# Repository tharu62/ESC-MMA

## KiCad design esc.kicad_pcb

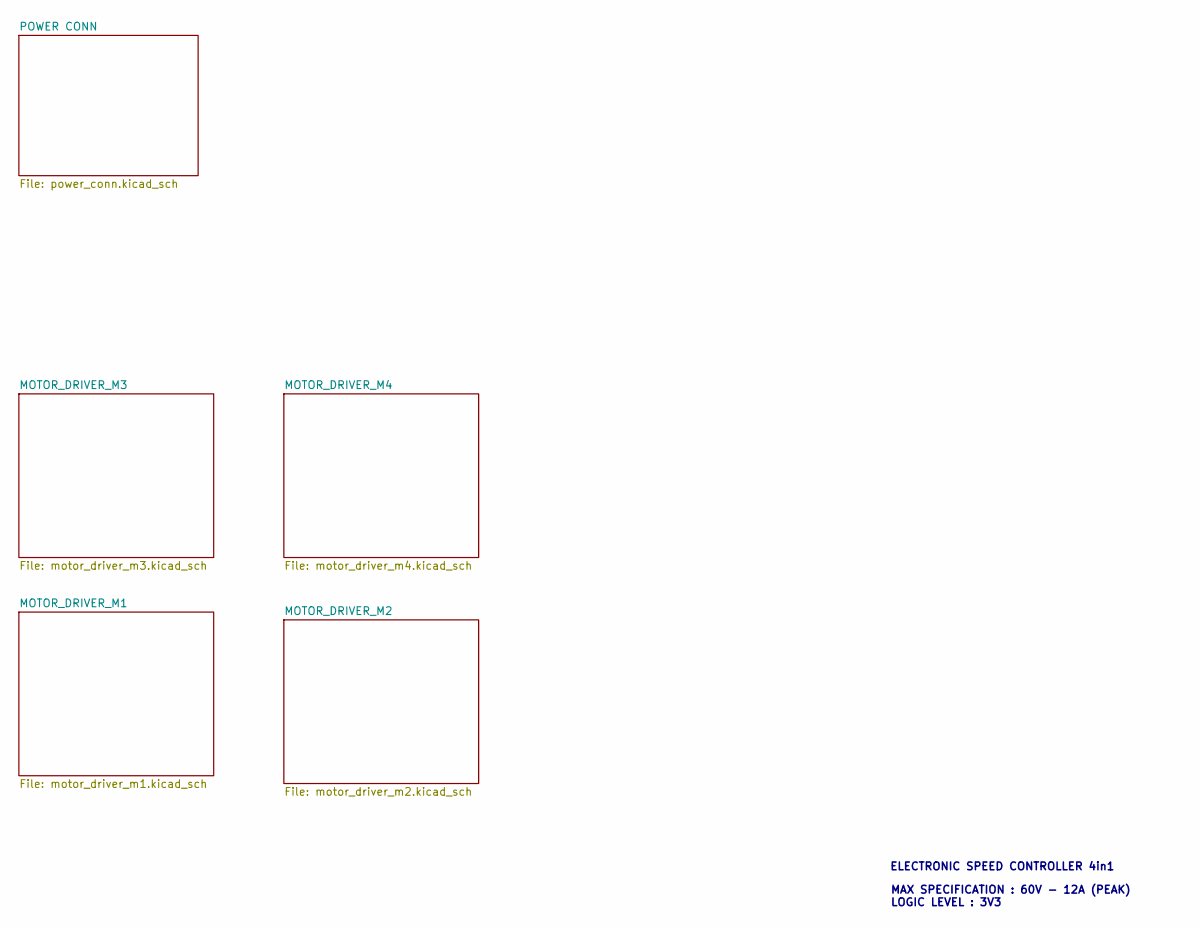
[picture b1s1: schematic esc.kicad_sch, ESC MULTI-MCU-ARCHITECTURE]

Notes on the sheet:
MAX SPECIFICATION : 60V - 12A (PEAK) LOGIC LEVEL : 3V3
ELECTRONIC SPEED CONTROLLER 4in1

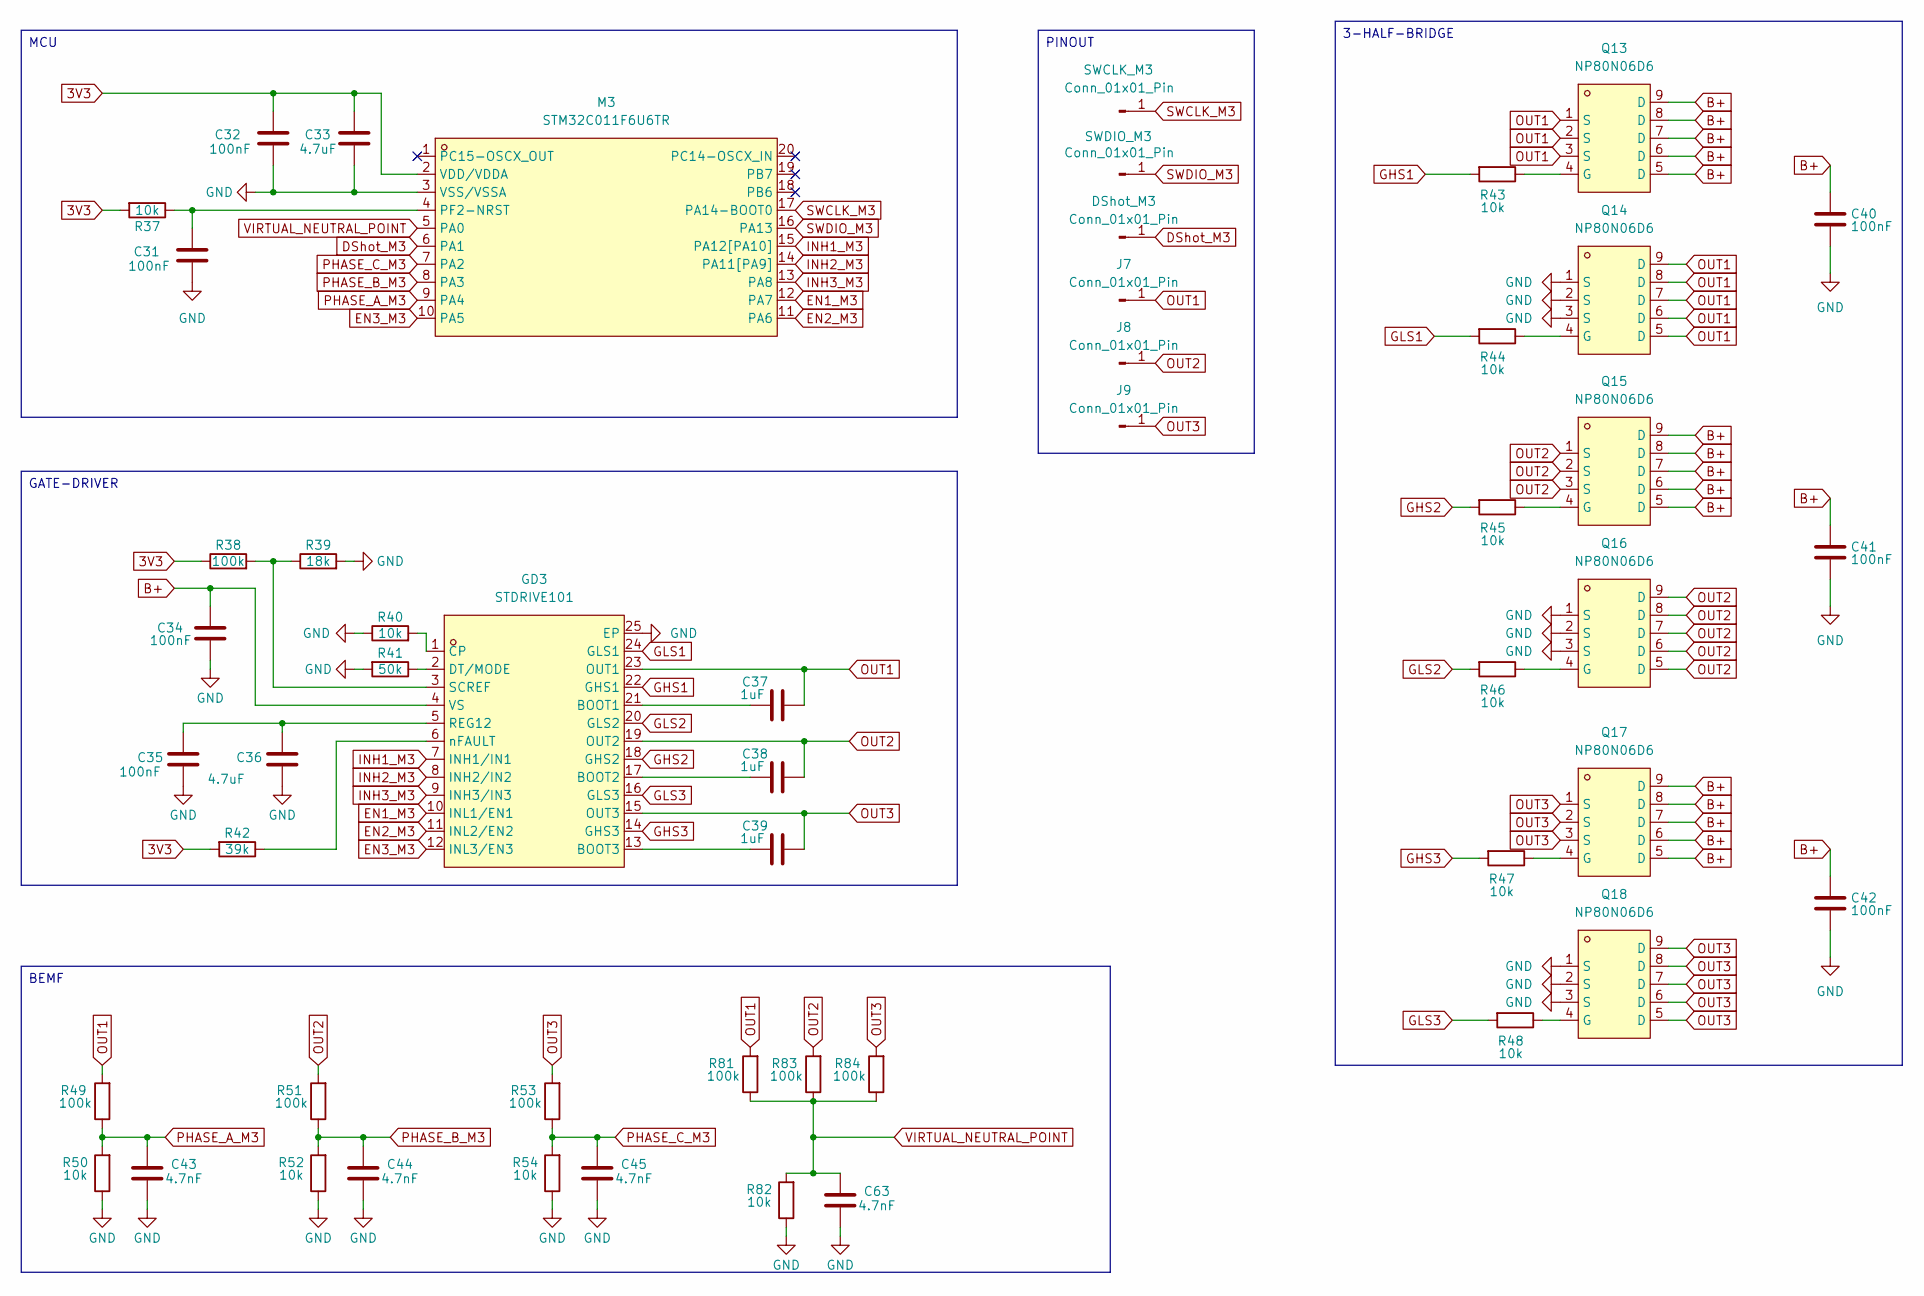
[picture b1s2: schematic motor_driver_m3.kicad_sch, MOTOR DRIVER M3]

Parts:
C31, C32, C34: 100nF; C0402
C33: 4.7uF; C0402
C35: 100nF; C0603
C36: 4.7uF; C0603
C37, C38, C39: 1uF; C0402
C40, C41, C42: 100nF; C1206
C43, C44, C45, C63: 4.7nF; C0402
DShot_M3: Conn_01x01_Pin
GD3: STDRIVE101; QFN-24_L4.0-W4.0-P0.50-BL-EP2.7; MPN STDRIVE101; LCSC Part C2969847
J7, J8, J9: Conn_01x01_Pin; Conn_01x01_Power
M3: STM32C011F6U6TR; UFQFPN-20_L3.0-W3.0-P0.50-TL; MPN STM32C011F6U6TR; LCSC Part C5456206
Q13, Q14, Q15, Q16, Q17, Q18: NP80N06D6; PDFN-8_L5.8-W5.0-P1.27-LS6.0-BL; MPN NP80N06D6; LCSC Part C2991153
R37, R40, R43, R44, R45, R46, R47, R48, R50, R52, R54, R82: 10k; R0402
R38, R49, R51, R53, R81, R83, R84: 100k; R0402
R39: 18k; R0402
R41: 50k; R0402
R42: 39k; R0402
SWCLK_M3: Conn_01x01_Pin
SWDIO_M3: Conn_01x01_Pin

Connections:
3V3: C32.1, C33.1, M3.2 (VDD/VDDA), R37.2, R38.1, R42.2; also elsewhere on the board
B+: C34.1, C40.1, C41.1, C42.1, GD3.4 (VS), Q13.5 (D), Q13.6 (D), Q13.7 (D), Q13.8 (D), Q13.9 (D), Q15.5 (D), Q15.6 (D), Q15.7 (D), Q15.8 (D), Q15.9 (D), Q17.5 (D), Q17.6 (D), Q17.7 (D), Q17.8 (D), Q17.9 (D); also elsewhere on the board
DShot_M3: DShot_M3.1 (Pin_1_1), M3.6 (PA1)
EN1_M3: GD3.10 (INL1/EN1), M3.12 (PA7)
EN2_M3: GD3.11 (INL2/EN2), M3.11 (PA6)
EN3_M3: GD3.12 (INL3/EN3), M3.10 (PA5)
GHS1: GD3.22 (GHS1), R43.2; also elsewhere on the board
GHS2: GD3.18 (GHS2), R45.2; also elsewhere on the board
GHS3: GD3.14 (GHS3), R47.2; also elsewhere on the board
GLS1: GD3.24 (GLS1), R44.2; also elsewhere on the board
GLS2: GD3.20 (GLS2), R46.2; also elsewhere on the board
GLS3: GD3.16 (GLS3), R48.2; also elsewhere on the board
GND: C31.2, C32.2, C33.2, C34.2, C35.2, C36.2, C40.2, C41.2, C42.2, C43.2, C44.2, C45.2, C63.2, GD3.25 (EP), M3.3 (VSS/VSSA), Q14.1 (S), Q14.2 (S), Q14.3 (S), Q16.1 (S), Q16.2 (S), Q16.3 (S), Q18.1 (S), Q18.2 (S), Q18.3 (S), R39.2, R40.1, R41.2, R50.1, R52.1, R54.1, R82.1; also elsewhere on the board
INH1_M3: GD3.7 (INH1/IN1), M3.15 (PA12[PA10])
INH2_M3: GD3.8 (INH2/IN2), M3.14 (PA11[PA9])
INH3_M3: GD3.9 (INH3/IN3), M3.13 (PA8)
unnamed: C37.2, GD3.21 (BOOT1)
unnamed: C38.2, GD3.17 (BOOT2)
unnamed: C39.2, GD3.13 (BOOT3)
unnamed: GD3.1 (CP), R40.2
unnamed: GD3.2 (DT/MODE), R41.1
unnamed: C35.1, C36.1, GD3.5 (REG12)
unnamed: GD3.3 (SCREF), R38.2, R39.1
unnamed: GD3.6 (nFAULT), R42.1
unnamed: C31.1, M3.4 (PF2-NRST), R37.1
unnamed: Q13.4 (G), R43.1
unnamed: Q14.4 (G), R44.1
unnamed: Q15.4 (G), R45.1
unnamed: Q16.4 (G), R46.1
unnamed: Q17.4 (G), R47.1
unnamed: Q18.4 (G), R48.1
OUT1: C37.1, GD3.23 (OUT1), J7.1 (Pin_1_1), Q13.1 (S), Q13.2 (S), Q13.3 (S), Q14.5 (D), Q14.6 (D), Q14.7 (D), Q14.8 (D), Q14.9 (D), R49.2, R81.2; also elsewhere on the board
OUT2: C38.1, GD3.19 (OUT2), J8.1 (Pin_1_1), Q15.1 (S), Q15.2 (S), Q15.3 (S), Q16.5 (D), Q16.6 (D), Q16.7 (D), Q16.8 (D), Q16.9 (D), R51.2, R83.2; also elsewhere on the board
OUT3: C39.1, GD3.15 (OUT3), J9.1 (Pin_1_1), Q17.1 (S), Q17.2 (S), Q17.3 (S), Q18.5 (D), Q18.6 (D), Q18.7 (D), Q18.8 (D), Q18.9 (D), R53.2, R84.2; also elsewhere on the board
PHASE_A_M3: C43.1, M3.9 (PA4), R49.1, R50.2
PHASE_B_M3: C44.1, M3.8 (PA3), R51.1, R52.2
PHASE_C_M3: C45.1, M3.7 (PA2), R53.1, R54.2
SWCLK_M3: M3.17 (PA14-BOOT0), SWCLK_M3.1 (Pin_1_1)
SWDIO_M3: M3.16 (PA13), SWDIO_M3.1 (Pin_1_1)
VIRTUAL_NEUTRAL_POINT: C63.1, M3.5 (PA0), R81.1, R82.2, R83.1, R84.1; also elsewhere on the board

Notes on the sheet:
PINOUT
GATE-DRIVER
3-HALF-BRIDGE
MCU
BEMF

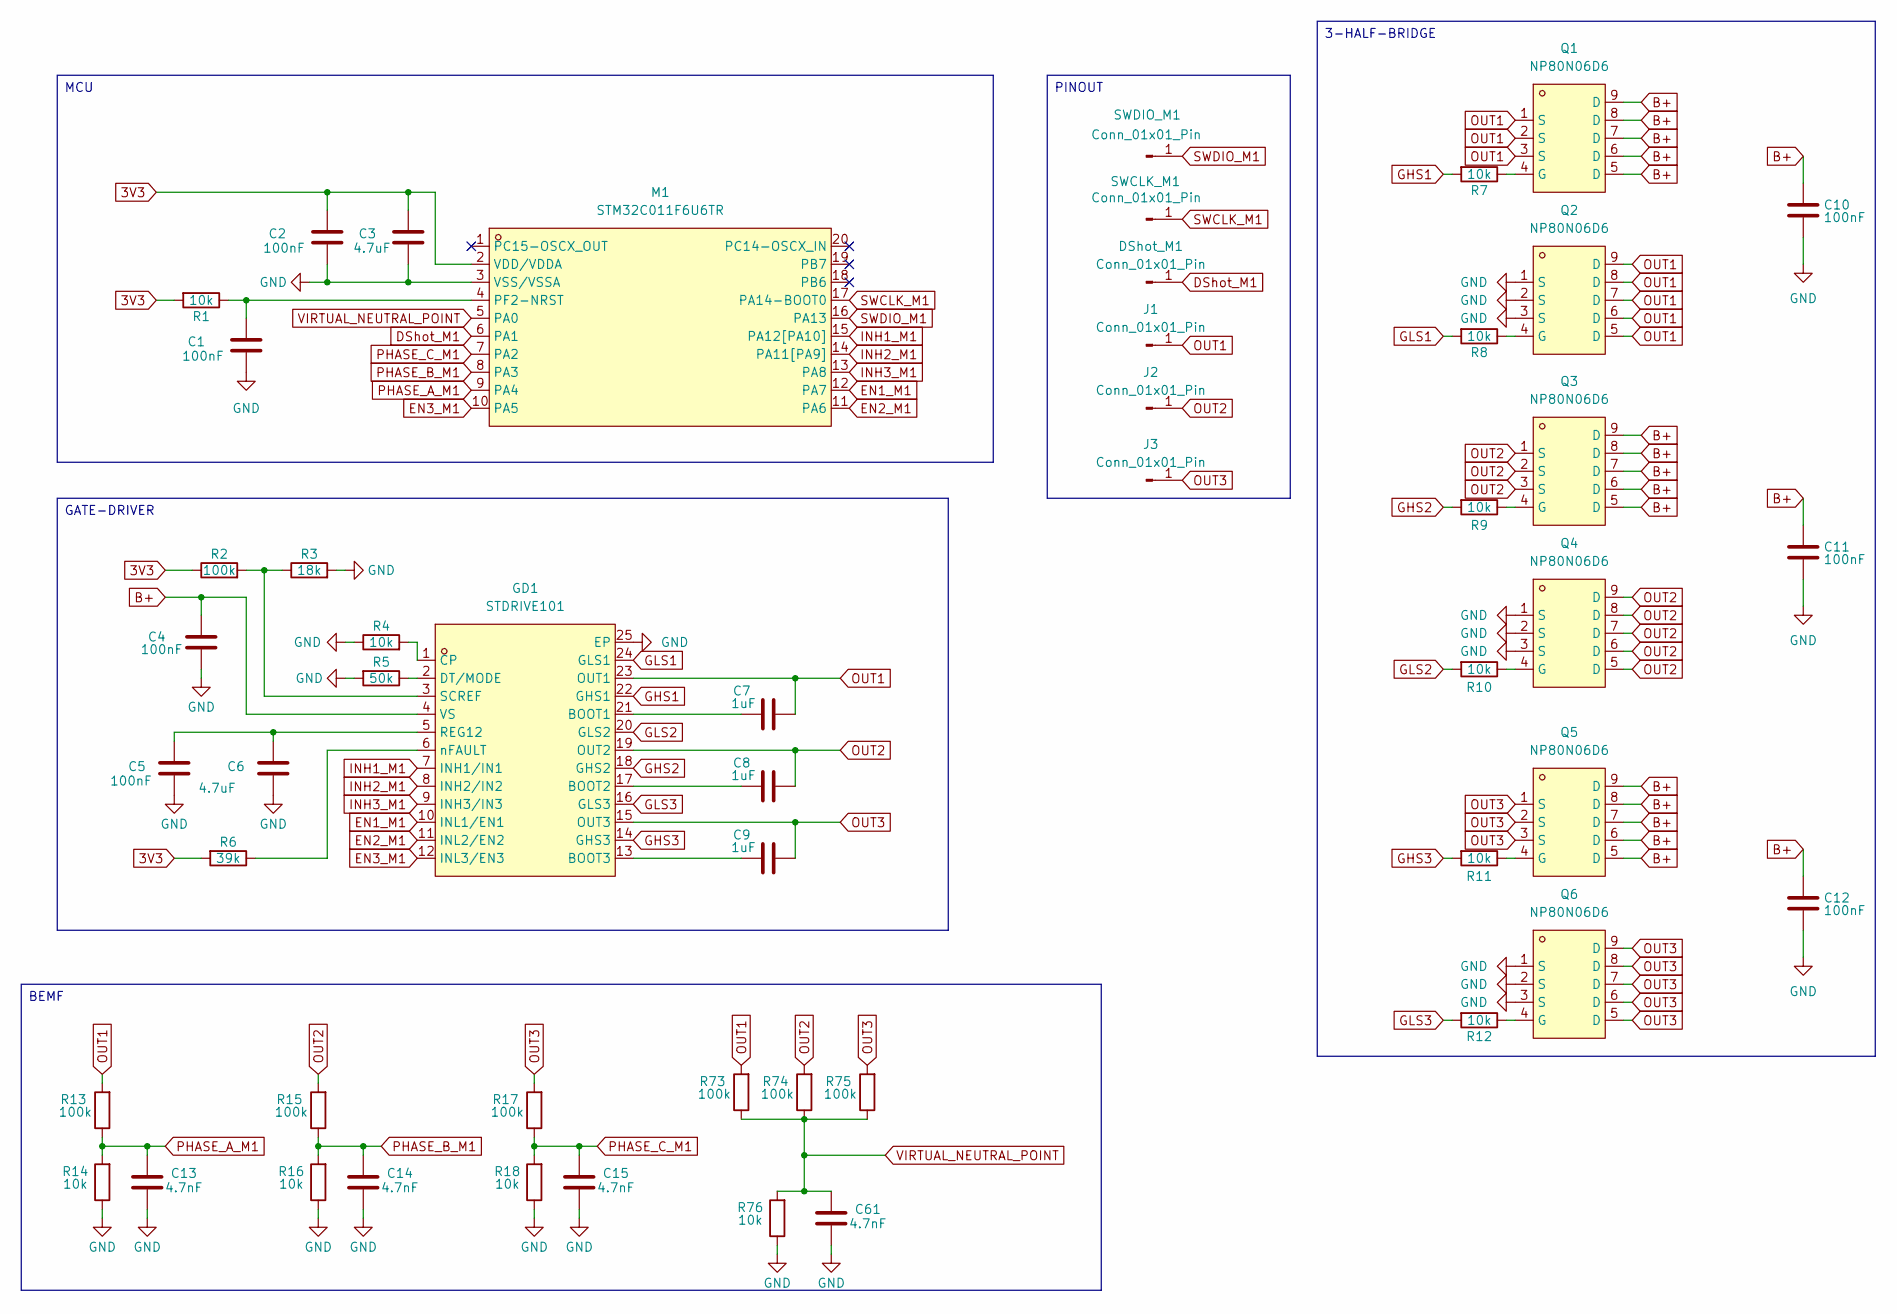
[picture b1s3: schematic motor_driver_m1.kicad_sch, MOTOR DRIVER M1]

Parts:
C1, C2, C4: 100nF; C0402
C3: 4.7uF; C0402
C5: 100nF; C0603
C6: 4.7uF; C0603
C7, C8, C9: 1uF; C0402
C10, C11, C12: 100nF; C1206
C13, C14, C15, C61: 4.7nF; C0402
DShot_M1: Conn_01x01_Pin
GD1: STDRIVE101; QFN-24_L4.0-W4.0-P0.50-BL-EP2.7; MPN STDRIVE101; LCSC Part C2969847
J1, J2, J3: Conn_01x01_Pin; Conn_01x01_Power
M1: STM32C011F6U6TR; UFQFPN-20_L3.0-W3.0-P0.50-TL; MPN STM32C011F6U6TR; LCSC Part C5456206
Q1, Q2, Q3, Q4, Q5, Q6: NP80N06D6; PDFN-8_L5.8-W5.0-P1.27-LS6.0-BL; MPN NP80N06D6; LCSC Part C2991153
R1, R4, R7, R8, R9, R10, R11, R12, R14, R16, R18, R76: 10k; R0402
R2, R13, R15, R17, R73, R74, R75: 100k; R0402
R3: 18k; R0402
R5: 50k; R0402
R6: 39k; R0402
SWCLK_M1: Conn_01x01_Pin
SWDIO_M1: Conn_01x01_Pin

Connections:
3V3: C2.1, C3.1, M1.2 (VDD/VDDA), R1.2, R2.1, R6.2; also elsewhere on the board
B+: C4.1, C10.1, C11.1, C12.1, GD1.4 (VS), Q1.5 (D), Q1.6 (D), Q1.7 (D), Q1.8 (D), Q1.9 (D), Q3.5 (D), Q3.6 (D), Q3.7 (D), Q3.8 (D), Q3.9 (D), Q5.5 (D), Q5.6 (D), Q5.7 (D), Q5.8 (D), Q5.9 (D); also elsewhere on the board
DShot_M1: DShot_M1.1 (Pin_1_1), M1.6 (PA1)
EN1_M1: GD1.10 (INL1/EN1), M1.12 (PA7)
EN2_M1: GD1.11 (INL2/EN2), M1.11 (PA6)
EN3_M1: GD1.12 (INL3/EN3), M1.10 (PA5)
GHS1: GD1.22 (GHS1), R7.2; also elsewhere on the board
GHS2: GD1.18 (GHS2), R9.2; also elsewhere on the board
GHS3: GD1.14 (GHS3), R11.2; also elsewhere on the board
GLS1: GD1.24 (GLS1), R8.2; also elsewhere on the board
GLS2: GD1.20 (GLS2), R10.2; also elsewhere on the board
GLS3: GD1.16 (GLS3), R12.2; also elsewhere on the board
GND: C1.2, C2.2, C3.2, C4.2, C5.2, C6.2, C10.2, C11.2, C12.2, C13.2, C14.2, C15.2, C61.2, GD1.25 (EP), M1.3 (VSS/VSSA), Q2.1 (S), Q2.2 (S), Q2.3 (S), Q4.1 (S), Q4.2 (S), Q4.3 (S), Q6.1 (S), Q6.2 (S), Q6.3 (S), R3.2, R4.1, R5.2, R14.1, R16.1, R18.1, R76.1; also elsewhere on the board
INH1_M1: GD1.7 (INH1/IN1), M1.15 (PA12[PA10])
INH2_M1: GD1.8 (INH2/IN2), M1.14 (PA11[PA9])
INH3_M1: GD1.9 (INH3/IN3), M1.13 (PA8)
unnamed: C7.2, GD1.21 (BOOT1)
unnamed: C8.2, GD1.17 (BOOT2)
unnamed: C9.2, GD1.13 (BOOT3)
unnamed: GD1.1 (CP), R4.2
unnamed: GD1.2 (DT/MODE), R5.1
unnamed: C5.1, C6.1, GD1.5 (REG12)
unnamed: GD1.3 (SCREF), R2.2, R3.1
unnamed: GD1.6 (nFAULT), R6.1
unnamed: C1.1, M1.4 (PF2-NRST), R1.1
unnamed: Q1.4 (G), R7.1
unnamed: Q2.4 (G), R8.1
unnamed: Q3.4 (G), R9.1
unnamed: Q4.4 (G), R10.1
unnamed: Q5.4 (G), R11.1
unnamed: Q6.4 (G), R12.1
OUT1: C7.1, GD1.23 (OUT1), J1.1 (Pin_1_1), Q1.1 (S), Q1.2 (S), Q1.3 (S), Q2.5 (D), Q2.6 (D), Q2.7 (D), Q2.8 (D), Q2.9 (D), R13.2, R73.2; also elsewhere on the board
OUT2: C8.1, GD1.19 (OUT2), J2.1 (Pin_1_1), Q3.1 (S), Q3.2 (S), Q3.3 (S), Q4.5 (D), Q4.6 (D), Q4.7 (D), Q4.8 (D), Q4.9 (D), R15.2, R74.2; also elsewhere on the board
OUT3: C9.1, GD1.15 (OUT3), J3.1 (Pin_1_1), Q5.1 (S), Q5.2 (S), Q5.3 (S), Q6.5 (D), Q6.6 (D), Q6.7 (D), Q6.8 (D), Q6.9 (D), R17.2, R75.2; also elsewhere on the board
PHASE_A_M1: C13.1, M1.9 (PA4), R13.1, R14.2
PHASE_B_M1: C14.1, M1.8 (PA3), R15.1, R16.2
PHASE_C_M1: C15.1, M1.7 (PA2), R17.1, R18.2
SWCLK_M1: M1.17 (PA14-BOOT0), SWCLK_M1.1 (Pin_1_1)
SWDIO_M1: M1.16 (PA13), SWDIO_M1.1 (Pin_1_1)
VIRTUAL_NEUTRAL_POINT: C61.1, M1.5 (PA0), R73.1, R74.1, R75.1, R76.2; also elsewhere on the board

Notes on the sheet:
GATE-DRIVER
MCU
3-HALF-BRIDGE
PINOUT
BEMF

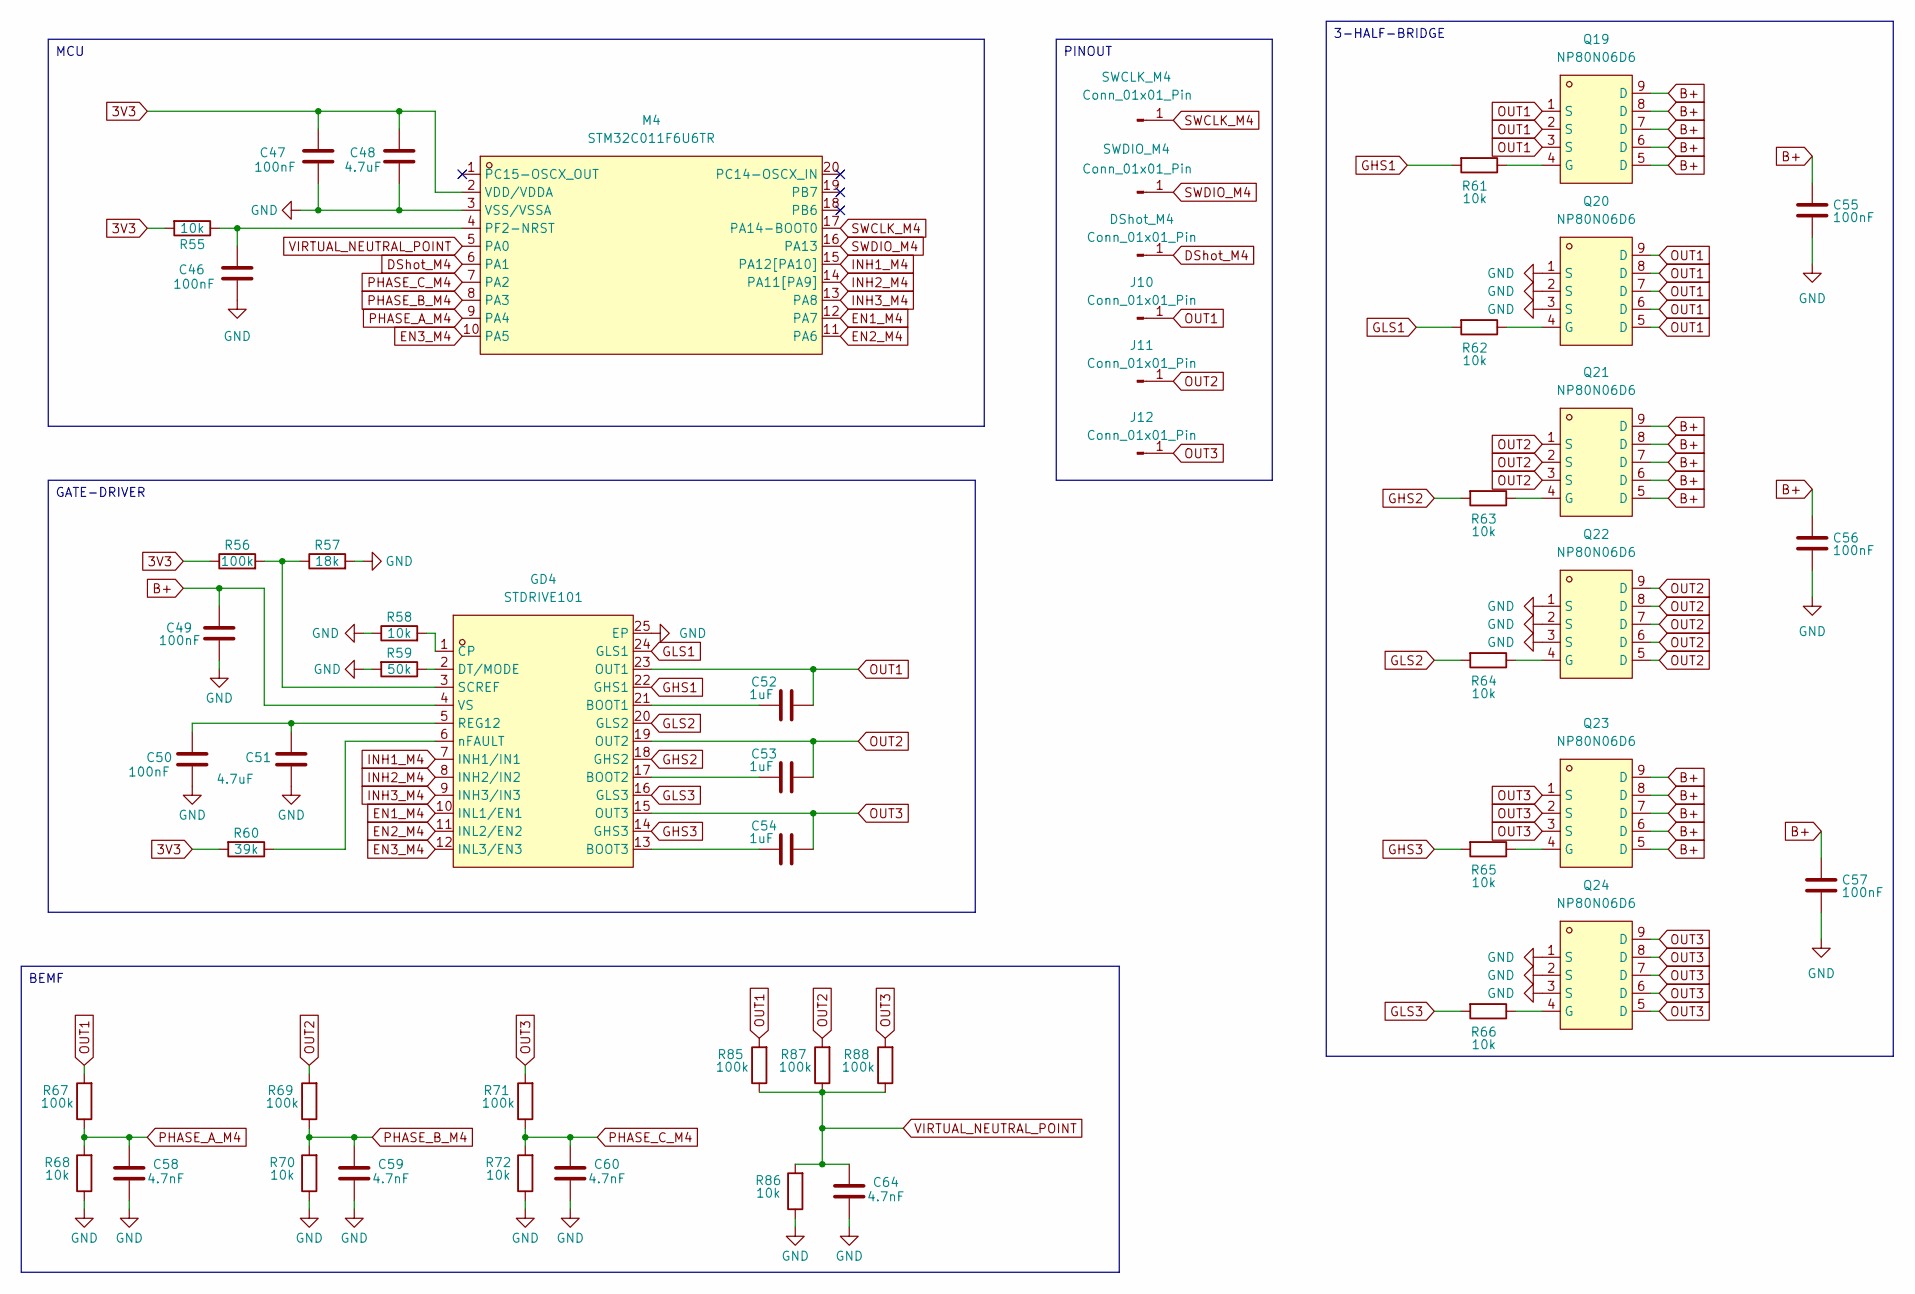
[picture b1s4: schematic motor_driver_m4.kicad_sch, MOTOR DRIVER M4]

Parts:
C46, C47, C49: 100nF; C0402
C48: 4.7uF; C0402
C50: 100nF; C0603
C51: 4.7uF; C0603
C52, C53, C54: 1uF; C0402
C55, C56, C57: 100nF; C1206
C58, C59, C60, C64: 4.7nF; C0402
DShot_M4: Conn_01x01_Pin
GD4: STDRIVE101; QFN-24_L4.0-W4.0-P0.50-BL-EP2.7; MPN STDRIVE101; LCSC Part C2969847
J10, J11, J12: Conn_01x01_Pin; Conn_01x01_Power
M4: STM32C011F6U6TR; UFQFPN-20_L3.0-W3.0-P0.50-TL; MPN STM32C011F6U6TR; LCSC Part C5456206
Q19, Q20, Q21, Q22, Q23, Q24: NP80N06D6; PDFN-8_L5.8-W5.0-P1.27-LS6.0-BL; MPN NP80N06D6; LCSC Part C2991153
R55, R58, R61, R62, R63, R64, R65, R66, R68, R70, R72, R86: 10k; R0402
R56, R67, R69, R71, R85, R87, R88: 100k; R0402
R57: 18k; R0402
R59: 50k; R0402
R60: 39k; R0402
SWCLK_M4: Conn_01x01_Pin
SWDIO_M4: Conn_01x01_Pin

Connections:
3V3: C47.1, C48.1, M4.2 (VDD/VDDA), R55.2, R56.1, R60.2; also elsewhere on the board
B+: C49.1, C55.1, C56.1, C57.1, GD4.4 (VS), Q19.5 (D), Q19.6 (D), Q19.7 (D), Q19.8 (D), Q19.9 (D), Q21.5 (D), Q21.6 (D), Q21.7 (D), Q21.8 (D), Q21.9 (D), Q23.5 (D), Q23.6 (D), Q23.7 (D), Q23.8 (D), Q23.9 (D); also elsewhere on the board
DShot_M4: DShot_M4.1 (Pin_1_1), M4.6 (PA1)
EN1_M4: GD4.10 (INL1/EN1), M4.12 (PA7)
EN2_M4: GD4.11 (INL2/EN2), M4.11 (PA6)
EN3_M4: GD4.12 (INL3/EN3), M4.10 (PA5)
GHS1: GD4.22 (GHS1), R61.2; also elsewhere on the board
GHS2: GD4.18 (GHS2), R63.2; also elsewhere on the board
GHS3: GD4.14 (GHS3), R65.2; also elsewhere on the board
GLS1: GD4.24 (GLS1), R62.2; also elsewhere on the board
GLS2: GD4.20 (GLS2), R64.2; also elsewhere on the board
GLS3: GD4.16 (GLS3), R66.2; also elsewhere on the board
GND: C46.2, C47.2, C48.2, C49.2, C50.2, C51.2, C55.2, C56.2, C57.2, C58.2, C59.2, C60.2, C64.2, GD4.25 (EP), M4.3 (VSS/VSSA), Q20.1 (S), Q20.2 (S), Q20.3 (S), Q22.1 (S), Q22.2 (S), Q22.3 (S), Q24.1 (S), Q24.2 (S), Q24.3 (S), R57.2, R58.1, R59.2, R68.1, R70.1, R72.1, R86.1; also elsewhere on the board
INH1_M4: GD4.7 (INH1/IN1), M4.15 (PA12[PA10])
INH2_M4: GD4.8 (INH2/IN2), M4.14 (PA11[PA9])
INH3_M4: GD4.9 (INH3/IN3), M4.13 (PA8)
unnamed: C52.2, GD4.21 (BOOT1)
unnamed: C53.2, GD4.17 (BOOT2)
unnamed: C54.2, GD4.13 (BOOT3)
unnamed: GD4.1 (CP), R58.2
unnamed: GD4.2 (DT/MODE), R59.1
unnamed: C50.1, C51.1, GD4.5 (REG12)
unnamed: GD4.3 (SCREF), R56.2, R57.1
unnamed: GD4.6 (nFAULT), R60.1
unnamed: C46.1, M4.4 (PF2-NRST), R55.1
unnamed: Q19.4 (G), R61.1
unnamed: Q20.4 (G), R62.1
unnamed: Q21.4 (G), R63.1
unnamed: Q22.4 (G), R64.1
unnamed: Q23.4 (G), R65.1
unnamed: Q24.4 (G), R66.1
OUT1: C52.1, GD4.23 (OUT1), J10.1 (Pin_1_1), Q19.1 (S), Q19.2 (S), Q19.3 (S), Q20.5 (D), Q20.6 (D), Q20.7 (D), Q20.8 (D), Q20.9 (D), R67.2, R85.2; also elsewhere on the board
OUT2: C53.1, GD4.19 (OUT2), J11.1 (Pin_1_1), Q21.1 (S), Q21.2 (S), Q21.3 (S), Q22.5 (D), Q22.6 (D), Q22.7 (D), Q22.8 (D), Q22.9 (D), R69.2, R87.2; also elsewhere on the board
OUT3: C54.1, GD4.15 (OUT3), J12.1 (Pin_1_1), Q23.1 (S), Q23.2 (S), Q23.3 (S), Q24.5 (D), Q24.6 (D), Q24.7 (D), Q24.8 (D), Q24.9 (D), R71.2, R88.2; also elsewhere on the board
PHASE_A_M4: C58.1, M4.9 (PA4), R67.1, R68.2
PHASE_B_M4: C59.1, M4.8 (PA3), R69.1, R70.2
PHASE_C_M4: C60.1, M4.7 (PA2), R71.1, R72.2
SWCLK_M4: M4.17 (PA14-BOOT0), SWCLK_M4.1 (Pin_1_1)
SWDIO_M4: M4.16 (PA13), SWDIO_M4.1 (Pin_1_1)
VIRTUAL_NEUTRAL_POINT: C64.1, M4.5 (PA0), R85.1, R86.2, R87.1, R88.1; also elsewhere on the board

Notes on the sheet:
BEMF
MCU
3-HALF-BRIDGE
GATE-DRIVER
PINOUT

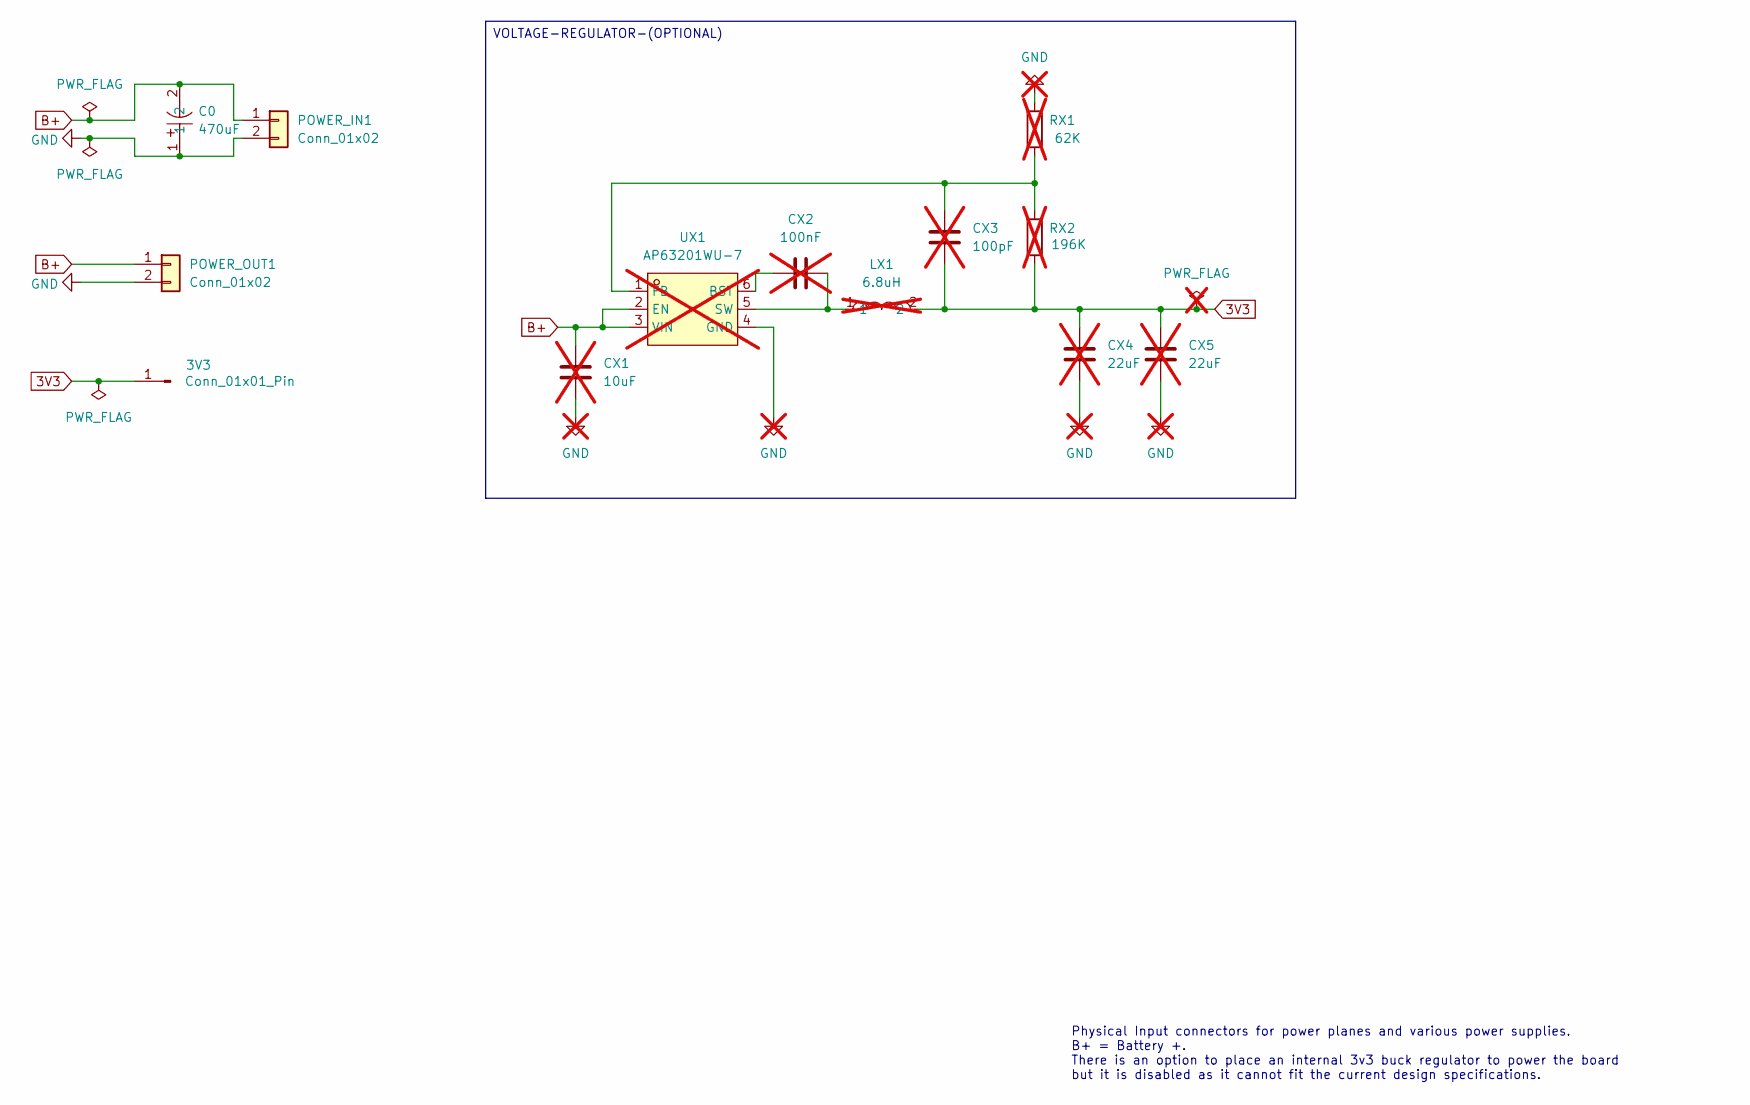
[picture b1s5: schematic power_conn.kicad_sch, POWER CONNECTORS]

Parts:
3V3: Conn_01x01_Pin
C0: 470uF; CAP-TH_BD10.0-P5.00-D0.6-FD_1; MPN ERG35V470M10X16; LCSC Part C48935386
CX1: 10uF; C1206; not fitted
CX2: 100nF; C0603; not fitted
CX3: 100pF; C0603; not fitted
CX4, CX5: 22uF; C0603; not fitted
LX1: 6.8uH; IND-SMD_L2.5-W2.0_FTC252010S; MPN FTC252012S6R8MBCA; LCSC Part C5832375; not fitted
POWER_IN1: Conn_01x02; Conn_01x01_power_x2
POWER_OUT1: Conn_01x02; Conn_01x01_power_x2
RX1: 62K; R0603; not fitted
RX2: 196K; R0805; not fitted
UX1: AP63201WU-7; TSOT-23-6_L2.9-W1.6-P0.95-LS2.8-BR; MPN AP63201WU-7; LCSC Part C2071044; not fitted

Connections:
3V3: 3V3.1 (Pin_1_1), CX3.2, CX4.1, CX5.1, LX1.2, RX2.1; also elsewhere on the board
B+: C0.2, CX1.1, POWER_IN1.1, POWER_OUT1.1, UX1.2 (EN), UX1.3 (VIN); also elsewhere on the board
GND: C0.1, CX1.2, CX4.2, CX5.2, POWER_IN1.2, POWER_OUT1.2, RX1.2, UX1.4 (GND); also elsewhere on the board
unnamed: CX2.1, UX1.6 (BST)
unnamed: CX2.2, LX1.1, UX1.5 (SW)
unnamed: CX3.1, RX1.1, RX2.2, UX1.1 (FB)

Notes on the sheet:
Physical Input connectors for power planes and various power supplies. B+ = Battery +. There is an option to place an internal 3v3 buck regulator to power the board but it is disabled as it cannot fit the current design specifications.
VOLTAGE-REGULATOR-(OPTIONAL)

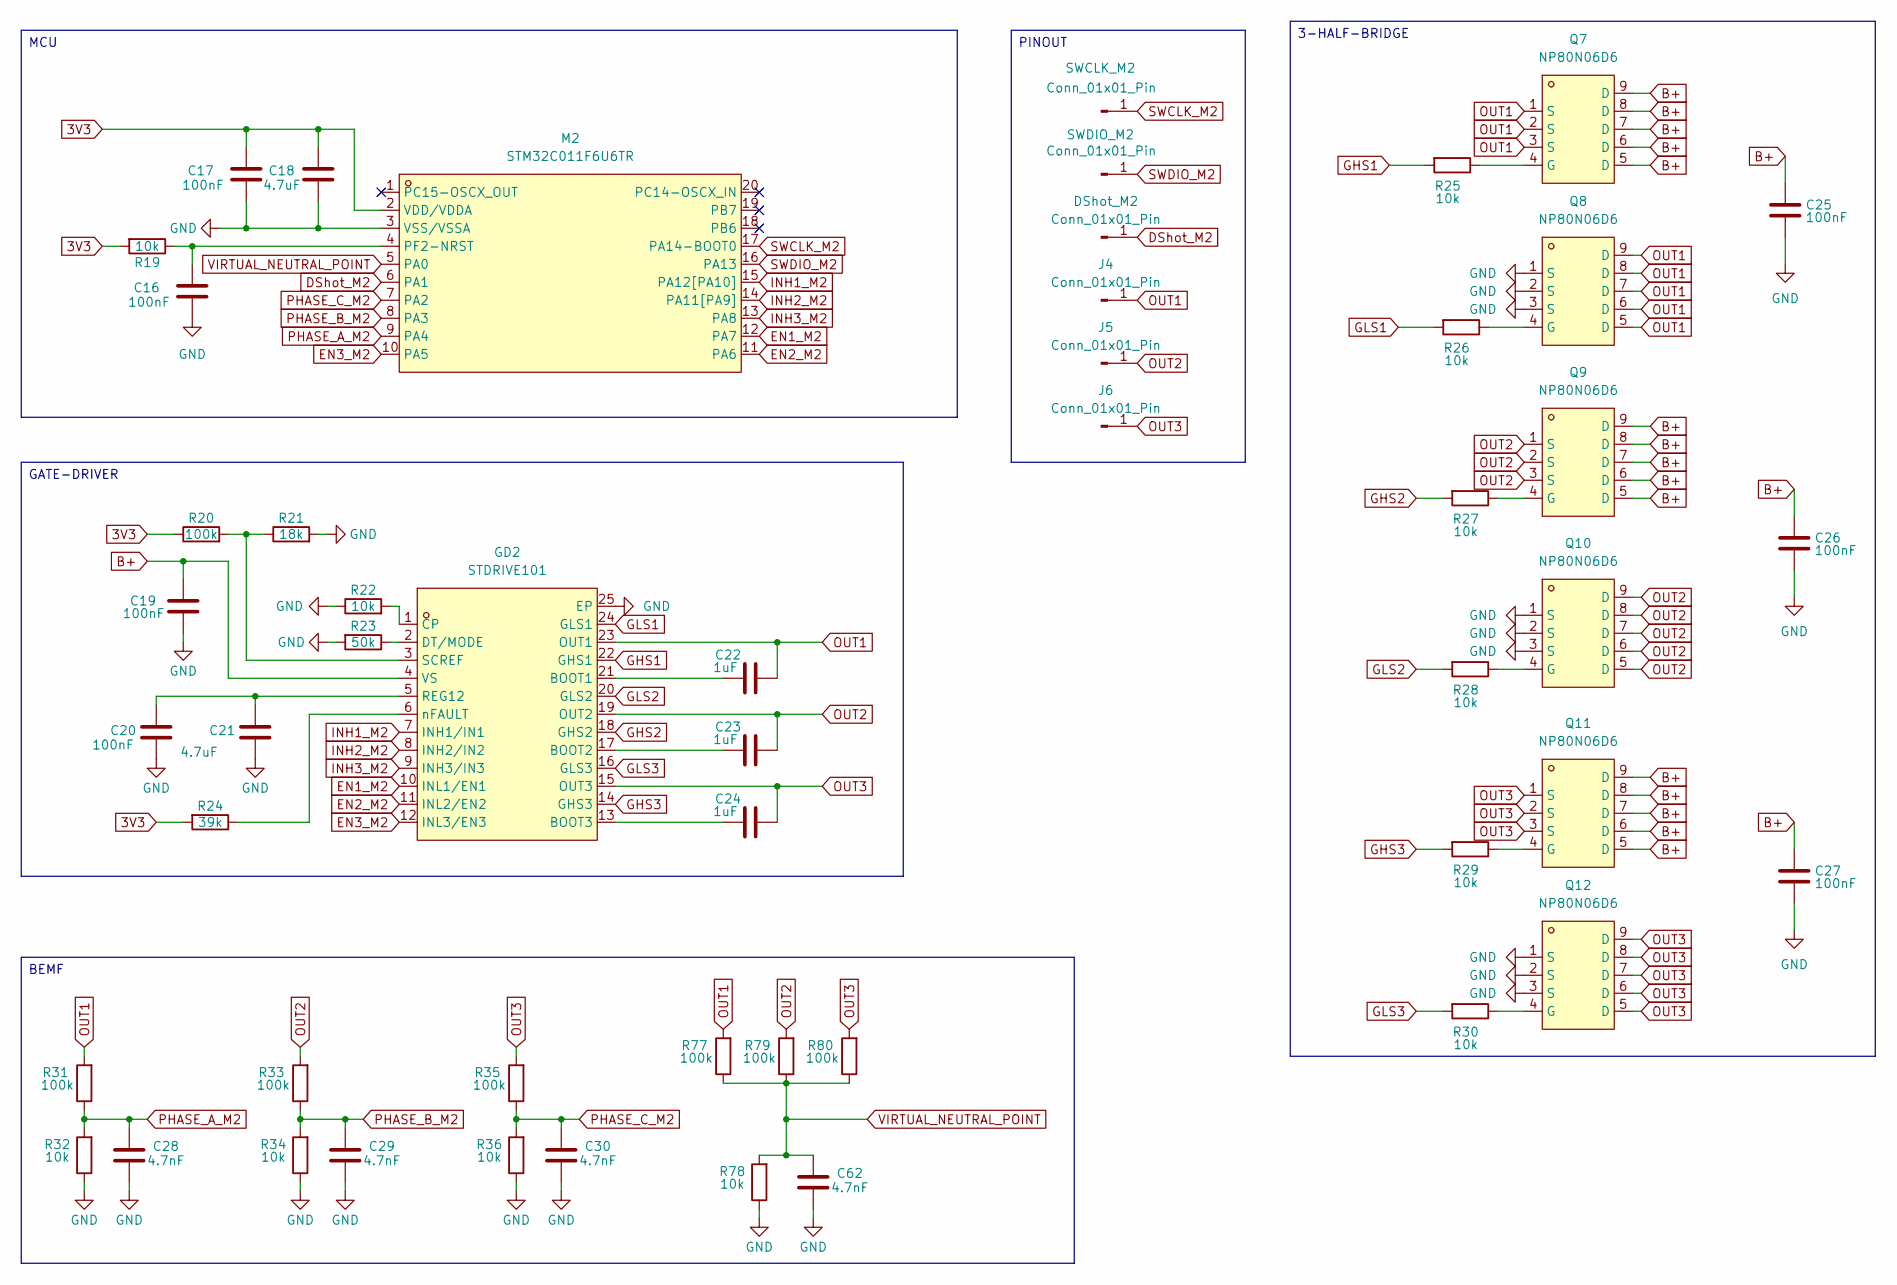
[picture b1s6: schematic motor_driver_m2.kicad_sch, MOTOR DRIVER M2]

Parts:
C16, C17, C19: 100nF; C0402
C18: 4.7uF; C0402
C20: 100nF; C0603
C21: 4.7uF; C0603
C22, C23, C24: 1uF; C0402
C25, C26, C27: 100nF; C1206
C28, C29, C30, C62: 4.7nF; C0402
DShot_M2: Conn_01x01_Pin
GD2: STDRIVE101; QFN-24_L4.0-W4.0-P0.50-BL-EP2.7; MPN STDRIVE101; LCSC Part C2969847
J4, J5, J6: Conn_01x01_Pin; Conn_01x01_Power
M2: STM32C011F6U6TR; UFQFPN-20_L3.0-W3.0-P0.50-TL; MPN STM32C011F6U6TR; LCSC Part C5456206
Q7, Q8, Q9, Q10, Q11, Q12: NP80N06D6; PDFN-8_L5.8-W5.0-P1.27-LS6.0-BL; MPN NP80N06D6; LCSC Part C2991153
R19, R22, R25, R26, R27, R28, R29, R30, R32, R34, R36, R78: 10k; R0402
R20, R31, R33, R35, R77, R79, R80: 100k; R0402
R21: 18k; R0402
R23: 50k; R0402
R24: 39k; R0402
SWCLK_M2: Conn_01x01_Pin
SWDIO_M2: Conn_01x01_Pin

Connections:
3V3: C17.1, C18.1, M2.2 (VDD/VDDA), R19.2, R20.1, R24.2; also elsewhere on the board
B+: C19.1, C25.1, C26.1, C27.1, GD2.4 (VS), Q7.5 (D), Q7.6 (D), Q7.7 (D), Q7.8 (D), Q7.9 (D), Q9.5 (D), Q9.6 (D), Q9.7 (D), Q9.8 (D), Q9.9 (D), Q11.5 (D), Q11.6 (D), Q11.7 (D), Q11.8 (D), Q11.9 (D); also elsewhere on the board
DShot_M2: DShot_M2.1 (Pin_1_1), M2.6 (PA1)
EN1_M2: GD2.10 (INL1/EN1), M2.12 (PA7)
EN2_M2: GD2.11 (INL2/EN2), M2.11 (PA6)
EN3_M2: GD2.12 (INL3/EN3), M2.10 (PA5)
GHS1: GD2.22 (GHS1), R25.2; also elsewhere on the board
GHS2: GD2.18 (GHS2), R27.2; also elsewhere on the board
GHS3: GD2.14 (GHS3), R29.2; also elsewhere on the board
GLS1: GD2.24 (GLS1), R26.2; also elsewhere on the board
GLS2: GD2.20 (GLS2), R28.2; also elsewhere on the board
GLS3: GD2.16 (GLS3), R30.2; also elsewhere on the board
GND: C16.2, C17.2, C18.2, C19.2, C20.2, C21.2, C25.2, C26.2, C27.2, C28.2, C29.2, C30.2, C62.2, GD2.25 (EP), M2.3 (VSS/VSSA), Q8.1 (S), Q8.2 (S), Q8.3 (S), Q10.1 (S), Q10.2 (S), Q10.3 (S), Q12.1 (S), Q12.2 (S), Q12.3 (S), R21.2, R22.1, R23.2, R32.1, R34.1, R36.1, R78.1; also elsewhere on the board
INH1_M2: GD2.7 (INH1/IN1), M2.15 (PA12[PA10])
INH2_M2: GD2.8 (INH2/IN2), M2.14 (PA11[PA9])
INH3_M2: GD2.9 (INH3/IN3), M2.13 (PA8)
unnamed: C22.2, GD2.21 (BOOT1)
unnamed: C23.2, GD2.17 (BOOT2)
unnamed: C24.2, GD2.13 (BOOT3)
unnamed: GD2.1 (CP), R22.2
unnamed: GD2.2 (DT/MODE), R23.1
unnamed: C20.1, C21.1, GD2.5 (REG12)
unnamed: GD2.3 (SCREF), R20.2, R21.1
unnamed: GD2.6 (nFAULT), R24.1
unnamed: C16.1, M2.4 (PF2-NRST), R19.1
unnamed: Q7.4 (G), R25.1
unnamed: Q8.4 (G), R26.1
unnamed: Q9.4 (G), R27.1
unnamed: Q10.4 (G), R28.1
unnamed: Q11.4 (G), R29.1
unnamed: Q12.4 (G), R30.1
OUT1: C22.1, GD2.23 (OUT1), J4.1 (Pin_1_1), Q7.1 (S), Q7.2 (S), Q7.3 (S), Q8.5 (D), Q8.6 (D), Q8.7 (D), Q8.8 (D), Q8.9 (D), R31.2, R77.2; also elsewhere on the board
OUT2: C23.1, GD2.19 (OUT2), J5.1 (Pin_1_1), Q9.1 (S), Q9.2 (S), Q9.3 (S), Q10.5 (D), Q10.6 (D), Q10.7 (D), Q10.8 (D), Q10.9 (D), R33.2, R79.2; also elsewhere on the board
OUT3: C24.1, GD2.15 (OUT3), J6.1 (Pin_1_1), Q11.1 (S), Q11.2 (S), Q11.3 (S), Q12.5 (D), Q12.6 (D), Q12.7 (D), Q12.8 (D), Q12.9 (D), R35.2, R80.2; also elsewhere on the board
PHASE_A_M2: C28.1, M2.9 (PA4), R31.1, R32.2
PHASE_B_M2: C29.1, M2.8 (PA3), R33.1, R34.2
PHASE_C_M2: C30.1, M2.7 (PA2), R35.1, R36.2
SWCLK_M2: M2.17 (PA14-BOOT0), SWCLK_M2.1 (Pin_1_1)
SWDIO_M2: M2.16 (PA13), SWDIO_M2.1 (Pin_1_1)
VIRTUAL_NEUTRAL_POINT: C62.1, M2.5 (PA0), R77.1, R78.2, R79.1, R80.1; also elsewhere on the board

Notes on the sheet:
BEMF
3-HALF-BRIDGE
MCU
GATE-DRIVER
PINOUT
